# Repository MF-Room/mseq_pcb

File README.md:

# MSeq PCB

KiCad 10 hardware design for [MSeq embedded](https://github.com/MF-Room/mseq_embedded),
the microcontroller implementation of the [MSeq](https://github.com/MF-Room/mseq) MIDI sequencer.

## Main specs
* MCU: STM32F413CHU6 (Arm Cortex-M4F, 100 MHz), 25 MHz HSE and 32.768 kHz LSE crystals
* MIDI: 2 × IN (H11L1M opto-isolated), 1 × OUT and 1 × THRU (74HCT125 buffered), 5-pin DIN sockets
* USB-C: USB-to-UART bridge (CP2102N) with ESD protection, also powers the board
* Storage: 16 Mbit SPI NOR flash (W25Q16JV) and 256 kbit SPI FRAM (MB85RS256B)
* Power: 5 V from USB, AMS1117-3.3 regulator, ON/OFF switch
* Controls: MASTER/SLAVE sync switch, RESET and BOOT buttons
* Headers: 10-pin SWD/JTAG (1.27 mm), 4-pin I2C header for a display
* LEDs: power, MIDI activity, USB TX/RX
* Board: 2 layers, 135.3 × 78.4 mm, 1.6 mm FR-4, all parts on the top side, made for JLCPCB assembly

## Related repositories
* [mseq_pcb_tb](https://github.com/MF-Room/mseq_pcb_tb) — test bench for the MSeq PCB
* [mseq_embedded](https://github.com/MF-Room/mseq_embedded) — microcontroller implementation of MSeq
* [mseq](https://github.com/MF-Room/mseq) — lightweight MIDI sequencer framework written in Rust

## License
Copyright © 2026 MF Room.

This hardware design is licensed under the CERN Open Hardware Licence Version 2 – Strongly Reciprocal
(SPDX-License-Identifier: `CERN-OHL-S-2.0`). See [LICENSE](LICENSE) for the full text.

Source location: https://github.com/MF-Room/mseq_pcb

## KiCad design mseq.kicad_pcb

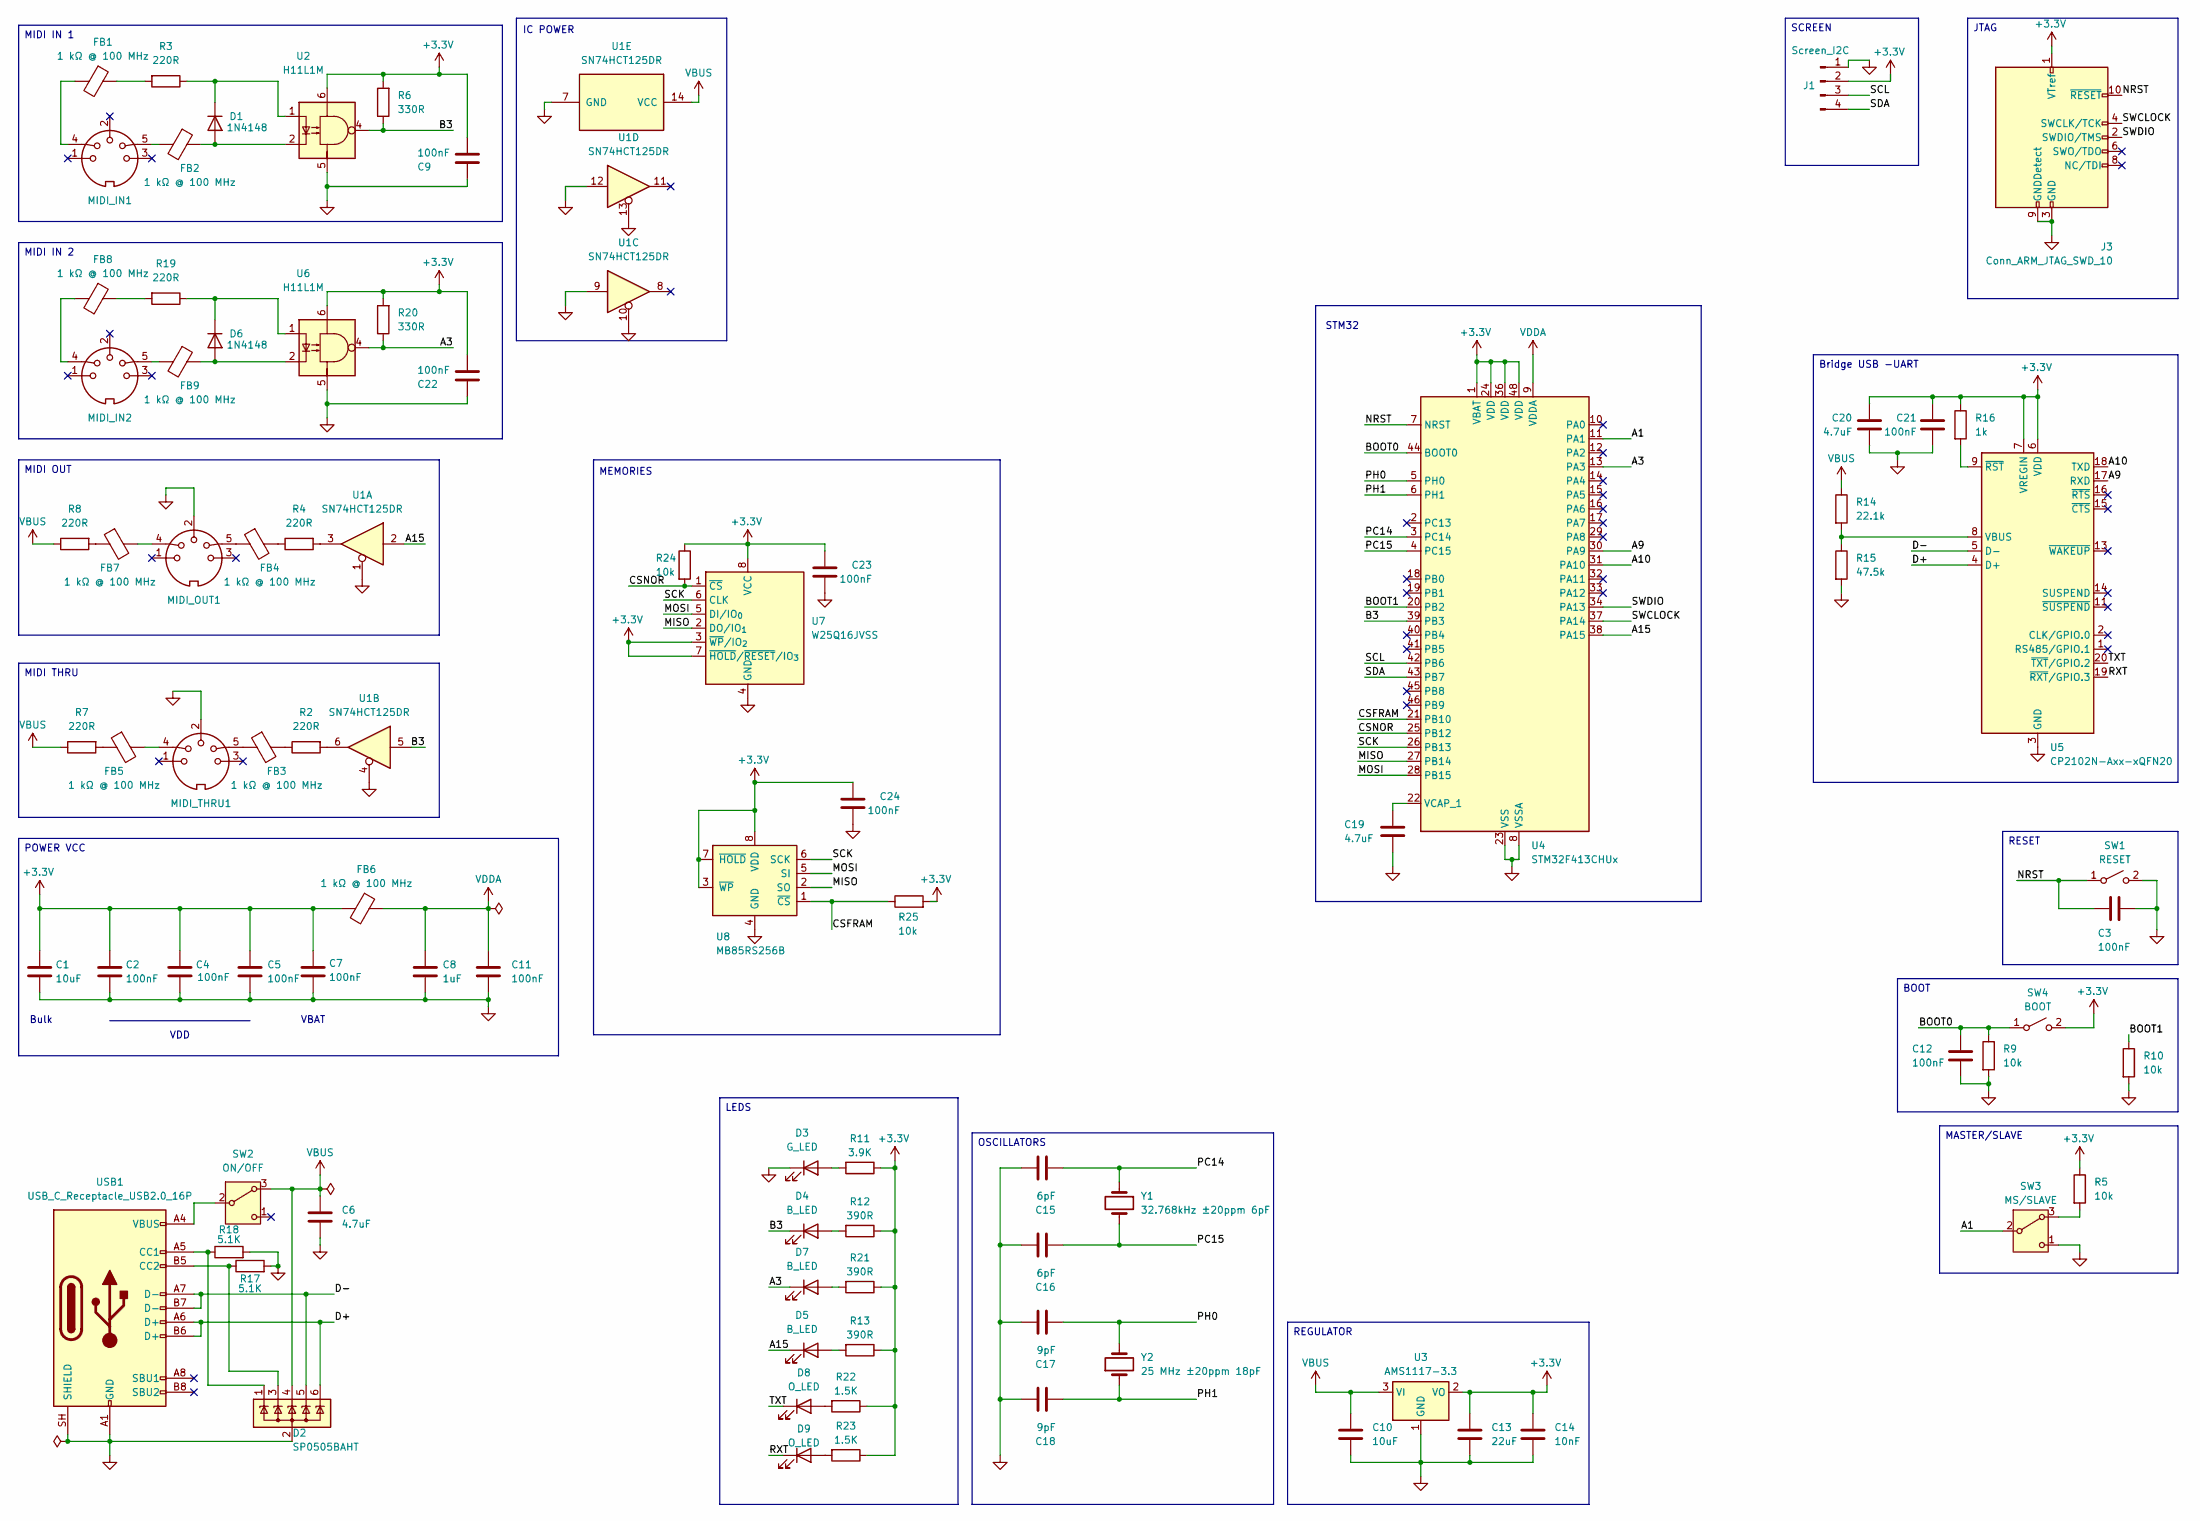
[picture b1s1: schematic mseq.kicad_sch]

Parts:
C1: 10uF; C_1206_3216Metric; Voltage 50; MPN CL31B106KAHNNNE; LCSC C14860
C2, C3, C4, C5, C7, C9, C11, C12, C21, C22, C23, C24: 100nF; C_0603_1608Metric; Voltage 50; MPN 06035C104JAT2A; LCSC C129176
C6, C19, C20: 4.7uF; C_1206_3216Metric; Voltage 25; MPN CL31B475KAHNNNE; LCSC C1872
C8: 1uF; C_0805_2012Metric; voltage rating 25; MPN CL21F105ZAFNNNE; LCSC C1761
C10: 10uF; C_1206_3216Metric; Voltage 25; MPN CL31B106KAHNNNE; LCSC C14860
C13: 22uF; C_1206_3216Metric; Voltage 25; MPN CL31A226KAHNNNE; LCSC C12891
C14: 10nF; C_0603_1608Metric; Voltage 50; MPN 06035C103JAT2A; LCSC C597189
C15, C16: 6pF; C_0603_1608Metric; MPN 0603CG6R0C500NT; LCSC C37474
C17, C18: 9pF; C_0805_2012Metric; MPN 0805CG9R0C500NT; LCSC C1844
D1, D6: 1N4148; D_SOD-123; MPN 1N4148W-E3-08; LCSC C727110
D2: SP0505BAHT; SOT-23-6; MPN SP0505BAHTG; LCSC C151299
D3: G_LED; LED_0603_1608Metric; MPN E6Q0603VGAC1UDA; LCSC C375576
D4, D5, D7: B_LED; LED_0603_1608Metric; MPN E6Q0603QBAC1UDA; LCSC C375575
D8, D9: O_LED; LED_0603_1608Metric; MPN TJ-S1608SW9T6ALC0A-A5; LCSC C601658
FB1, FB2, FB3, FB4, FB5, FB6, FB7, FB8, FB9: 1 kΩ @ 100 MHz; L_TDK_MLZ1608; MPN MMZ1608R102ATA00; LCSC C89445
J1: Screen_I2C; PinSocket_1x04_P2.54mm_Vertical; MPN HX PM2.54-1x4P ZC H5.7; LCSC C46061763
J3: Conn_ARM_JTAG_SWD_10; PinHeader_2x05_P1.27mm_Vertical_SMD; MPN FTSH-105-01-L-DV-K-TR; LCSC C448647
MIDI_IN1, MIDI_IN2: DIN-5_180degree; DIN-504; MPN DIN-504; LCSC C23689428
MIDI_OUT1: DIN-5_180degree; DIN-504; MPN DIN-504; LCSC C23689428
MIDI_THRU1: DIN-5_180degree; DIN-504; MPN DIN-504; LCSC C23689428
R2, R3, R4, R7, R8, R19: 220R; R_0603_1608Metric; MPN 0603WAF2200T5E; LCSC C22962
R5, R9, R10, R24, R25: 10k; R_0603_1608Metric; MPN RCA0310KJLF; LCSC C22369937
R6, R20: 330R; R_0603_1608Metric; MPN CRCW0603330RJNEA; LCSC C844777
R11: 3.9K; R_0805_2012Metric; MPN 0805W8F3901T5E; LCSC C17614
R12, R13, R21: 390R; R_0805_2012Metric; MPN 0805W8F3900T5E; LCSC C17655
R14: 22.1k; R_0805_2012Metric; MPN RT0805BRD0722K1L; LCSC C865310
R15: 47.5k; R_0603_1608Metric; MPN 0603WAF4752T5E; LCSC C23061
R16: 1k; R_0603_1608Metric; MPN 0603WAF1001T5E; LCSC C21190
R17, R18: 5.1K; R_0603_1608Metric; MPN 0603WAF5101T5E; LCSC C23186
R22, R23: 1.5K; R_0805_2012Metric; MPN 0805W8F1501T5E; LCSC C4310
SW1: RESET; SW2_1825027-A_TEC; MPN 1825027-5; LCSC C86476
SW2: ON/OFF; SW_Slide_SPDT_Angled_CK_OS102011MA1Q; MPN OS102011MA1QS1; LCSC C221530
SW3: MS/SLAVE; SW_Slide_SPDT_Angled_CK_OS102011MA1Q; MPN OS102011MA1QS1; LCSC C221530
SW4: BOOT; SW2_1825027-A_TEC; MPN 1825027-5; LCSC C86476
U1: SN74HCT125DR; SOIC-14_3.9x8.7mm_P1.27mm; MPN SN74HCT125DR; LCSC C352957
U2, U6: H11L1M; SMDIP-6_W9.53mm; MPN H11L1SM; LCSC C899473
U3: AMS1117-3.3; SOT-223-3_TabPin2; MPN AMS1117-3.3; LCSC C6186
U4: STM32F413CHUx; QFN-48-1EP_7x7mm_P0.5mm_EP5.6x5.6mm; MPN STM32F413CHU6; LCSC C1337761
U5: CP2102N-Axx-xQFN20; SiliconLabs_QFN-20-1EP_3x3mm_P0.5mm_EP1.8x1.8mm; MPN CP2102N-A02-GQFN20R; LCSC C969913
U7: W25Q16JVSS; SOIC-8_5.3x5.3mm_P1.27mm; MPN W25Q16JVSSIQ; LCSC C131025
U8: MB85RS256B; SOIC-8_3.9x4.9mm_P1.27mm; MPN MB85RS256BPNF-G-JNERE1; LCSC C8742
USB1: USB_C_Receptacle_USB2.0_16P; USB_C_Receptacle_HRO_TYPE-C-31-M-12; MPN TYPE-C-31-M-12; LCSC C165948
Y1: 32.768kHz ±20ppm 6pF; Crystal_SMD_MicroCrystal_CC7V-T1A-2Pin_3.2x1.5mm; MPN CM7V-T1A-32.768kHz-6pF-20PPM-TA-QC; LCSC C5366534
Y2: 25 MHz ±20ppm 18pF; Crystal_SMD_5032-2Pin_5.0x3.2mm; MPN ABM3-25.000MHZ-D2Y-T; LCSC C148312

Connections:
+3.3V: C1.1, C2.1, C4.1, C5.1, C7.1, C9.1, C13.1, C14.1, C20.1, C21.2, C22.1, C23.2, C24.2, FB6.2, J1.2, J3.1 (VTref), R5.1, R6.2, R11.1, R12.1, R13.1, R16.1, R20.2, R21.1, R22.1, R23.1, R24.1, R25.2, SW4.2 (B), U2.6, U3.2 (VO), U4.1 (VBAT), U4.24 (VDD), U4.36 (VDD), U4.48 (VDD), U5.6 (VDD), U5.7 (VREGIN), U6.6, U7.3 (~WP/IO_{2}), U7.7 (~HOLD/~RESET/IO_{3}), U7.8 (VCC), U8.3 (~WP), U8.7 (~HOLD), U8.8 (VDD)
/A1: SW3.2 (B), U4.11 (PA1)
/A3: D7.1 (K), R20.1, U4.13 (PA3), U6.4
/A9: U4.30 (PA9), U5.17 (RXD)
/A10: U4.31 (PA10), U5.18 (TXD)
/A15: D5.1 (K), U1.2, U4.38 (PA15)
/B3: D4.1 (K), R6.1, U1.5, U2.4, U4.39 (PB3)
/BOOT0: C12.1, R9.1, SW4.1 (A), U4.44 (BOOT0)
/BOOT1: R10.1, U4.20 (PB2)
/CSFRAM: R25.1, U4.21 (PB10), U8.1 (~CS)
/CSNOR: R24.2, U4.25 (PB12), U7.1 (~CS)
/D+: D2.6 (K), U5.4 (D+), USB1.A6 (D+), USB1.B6 (D+)
/D-: D2.5 (K), U5.5 (D-), USB1.A7 (D-), USB1.B7 (D-)
/MISO: U4.27 (PB14), U7.2 (DO/IO_{1}), U8.2 (SO)
/MOSI: U4.28 (PB15), U7.5 (DI/IO_{0}), U8.5 (SI)
/NRST: C3.1, J3.10 (~RESET), SW1.1 (A), U4.7 (NRST)
/PC14: C15.1, U4.3 (PC14), Y1.1
/PC15: C16.1, U4.4 (PC15), Y1.2
/PH0: C17.1, U4.5 (PH0), Y2.2
/PH1: C18.1, U4.6 (PH1), Y2.1
/RXT: D9.1 (K), U5.19 (~RXT/GPIO.3)
/SCK: U4.26 (PB13), U7.6 (CLK), U8.6 (SCK)
/SCL: J1.3, U4.42 (PB6)
/SDA: J1.4, U4.43 (PB7)
/SWCLOCK: J3.4 (SWCLK/TCK), U4.37 (PA14)
/SWDIO: J3.2 (SWDIO/TMS), U4.34 (PA13)
/TXT: D8.1 (K), U5.20 (~TXT/GPIO.2)
GND: C1.2, C2.2, C3.2, C4.2, C5.2, C6.2, C7.2, C8.2, C9.2, C10.2, C11.2, C12.2, C13.2, C14.2, C15.2, C16.2, C17.2, C18.2, C19.2, C20.2, C21.1, C22.2, C23.1, C24.1, D2.2 (A), D3.1 (K), J1.1, J3.3 (GND), J3.5 (GND), J3.9 (GNDDetect), MIDI_OUT1.2, MIDI_THRU1.2, R9.2, R10.2, R15.2, R17.2, R18.2, SW1.2 (B), SW3.1 (C), U1.1, U1.4, U1.7 (GND), U1.9, U1.10, U1.12, U1.13, U2.5, U3.1 (GND), U4.8 (VSSA), U4.23 (VSS), U4.35 (VSS), U4.47 (VSS), U4.49 (VSS), U5.3 (GND), U5.12 (GND), U5.21 (GND), U6.5, U7.4 (GND), U8.4 (GND), USB1.A1 (GND), USB1.A12 (GND), USB1.B1 (GND), USB1.B12 (GND), USB1.SH (SHIELD)
unnamed: D1.2 (A), FB2.1, U2.2
unnamed: D1.1 (K), R3.1, U2.1
unnamed: D3.2 (A), R11.2
unnamed: D4.2 (A), R12.2
unnamed: D5.2 (A), R13.2
unnamed: D6.2 (A), FB9.1, U6.2
unnamed: D6.1 (K), R19.1, U6.1
unnamed: D7.2 (A), R21.2
unnamed: D8.2 (A), R22.2
unnamed: D9.2 (A), R23.2
unnamed: FB1.1, R3.2
unnamed: FB1.2, MIDI_IN1.4
unnamed: FB2.2, MIDI_IN1.5
unnamed: FB3.1, MIDI_THRU1.5
unnamed: FB3.2, R2.1
unnamed: FB4.1, MIDI_OUT1.5
unnamed: FB4.2, R4.1
unnamed: FB5.1, R7.2
unnamed: FB5.2, MIDI_THRU1.4
unnamed: FB7.1, R8.2
unnamed: FB7.2, MIDI_OUT1.4
unnamed: FB8.1, R19.2
unnamed: FB8.2, MIDI_IN2.4
unnamed: FB9.2, MIDI_IN2.5
unnamed: R2.2, U1.6
unnamed: R4.2, U1.3
unnamed: SW2.2 (B), USB1.A4 (VBUS), USB1.A9 (VBUS), USB1.B4 (VBUS), USB1.B9 (VBUS)
unnamed: R5.2, SW3.3 (A)
unnamed: C19.1, U4.22 (VCAP_1)
unnamed: R14.2, R15.1, U5.8 (VBUS)
unnamed: R16.2, U5.9 (~RST)
unnamed: D2.1 (K), R18.1, USB1.A5 (CC1)
unnamed: D2.3 (K), R17.1, USB1.B5 (CC2)
VBUS: C6.1, C10.1, D2.4 (K), R7.1, R8.1, R14.1, SW2.3 (A), U1.14 (VCC), U3.3 (VI)
VDDA: C8.1, C11.1, FB6.1, U4.9 (VDDA)

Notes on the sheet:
VDD
MEMORIES
VBAT
Bulk
STM32
IC POWER
SCREEN
MIDI IN 2
MIDI IN 1
MASTER/SLAVE
LEDS
MIDI OUT
REGULATOR
Bridge USB -UART
MIDI THRU
BOOT
POWER VCC
OSCILLATORS
JTAG
RESET

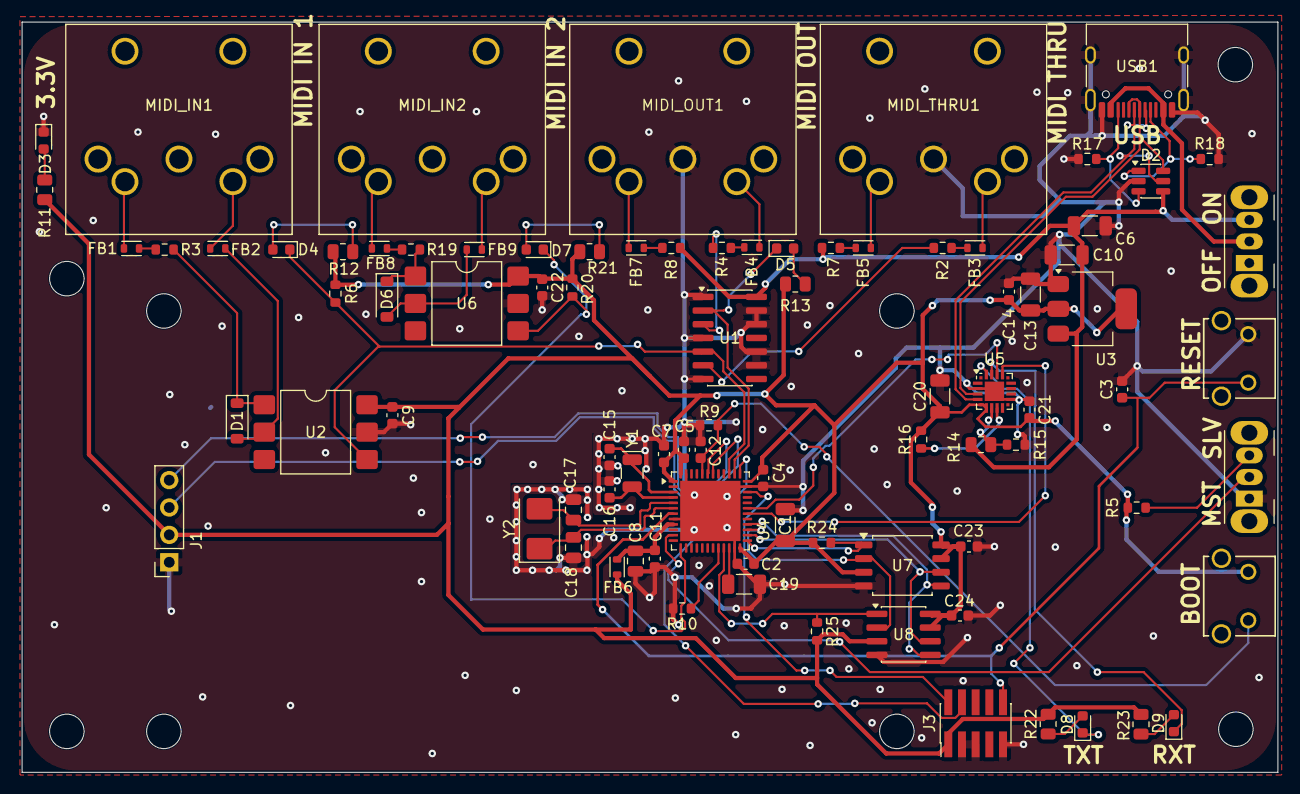
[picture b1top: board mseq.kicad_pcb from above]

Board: 2 copper layers, 116.5 x 69.6 mm, 87 parts (0 on the bottom side), 63 nets.

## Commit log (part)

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2025-10-19 advance schematic
2025-10-29 Power updated
2025-11-09 schematic ready for review
2025-11-09 work on footprints
2025-11-11 Bug fixed
2025-11-12 sch done
2025-11-20 Updated with new mcu
2025-11-22 MPN added
2025-11-30 MPN capacitor almost done
2025-11-30 Bypass capacitor in VCC don
2025-12-02 MPN almost done
2025-12-03 MPN for bypass capacitors done
2025-12-10 Resistor for MIDI done
2025-12-24 MPN for resistors and diodes added
2025-12-31 MPN for LED resistor done
2026-01-02 Schematic finished. MPN OK. FPs OK.
2026-01-24 Placement done.
2026-02-28 90% Routing
2026-02-28 finish routing
2026-03-06 Last DRC Check
2026-03-08 v0.1.0 done
2026-03-18 LCSC added and bom script added
2026-03-18 Missing LCSC added
2026-03-26 LCSC Part Change, need MCP/MPN
2026-03-26 Wip MPN
2026-03-26 MPN update wip
2026-03-26 Almost done
2026-05-01 USB connector changed
2026-05-01 WIP, need to make the board bigger
2026-05-01 README cleaned
2026-05-31 Moved to new version of kicad
2026-05-31 LED reversed and MIDI out reversed
2026-06-27 USB bug fixed and new JTAG connector
2026-06-28 Second midi in added
